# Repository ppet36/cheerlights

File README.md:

# Cheerlights coaster

Sources and models for Cheerlights coaster. Here is schematic + PCB layout files for my build of Cheerlights coaster as well as OpenSCAD model for enclosure and source code for ESP8266.

Build video https://www.youtube.com/watch?v=22OCCYykrT4

You need ESP8266-01 from eBay, WS2812B RGB digital LED, 3x10K resistor, 2x100n + 2x470u capacitor, 2x4 PINHD connector + standard 5.5/2.1 power conector (male and female) - beware that i made mistake in design schematic/PCB and power connector has -inside and +outside of the plug.

For build in Arduino you need FastLED library; https://github.com/FastLED/FastLED

### Some images

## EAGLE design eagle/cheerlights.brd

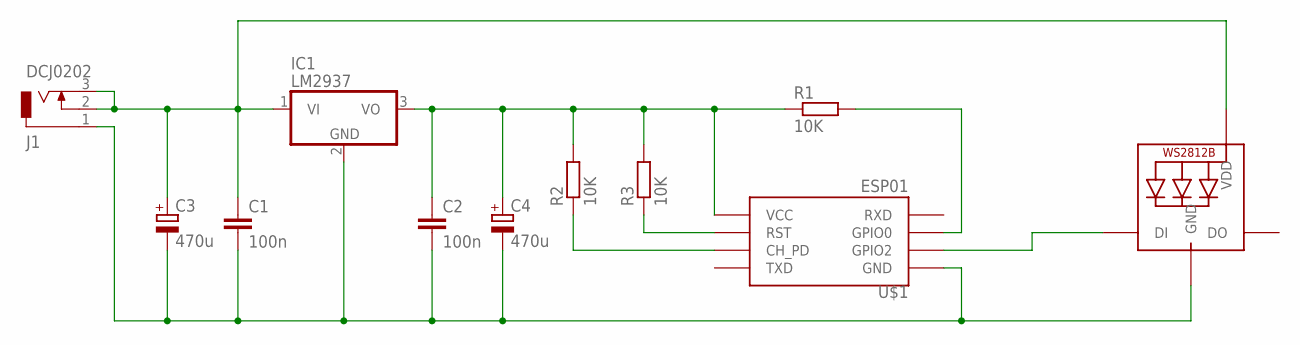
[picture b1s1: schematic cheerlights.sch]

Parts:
C1, C2: 100n; C050-025X075
C3, C4: 470u; E5-10,5
IC1: LM2937; TO220H
J1: DCJ0202
LED1: WS2812B_5050N; WS2812B-NARROW
R1: 10K; 0207/10
R2, R3: 10K; 0207/15
U$1: ESP01

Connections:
unnamed: C1.1, C3.+, IC1.1 (VI), J1.2, J1.3, LED1.1-VDD (VDD)
unnamed: C1.2, C2.2, C3.-, C4.-, IC1.2 (GND), J1.1, LED1.3-GND (GND), U$1.GND
unnamed: C2.1, C4.+, IC1.3 (VO), R1.1, R2.2, R3.2, U$1.VCC
unnamed: R1.2, U$1.GPIO0
unnamed: R3.1, U$1.RST
unnamed: R2.1, U$1.CH_PD
unnamed: LED1.4-DIN (DI), U$1.GPIO2

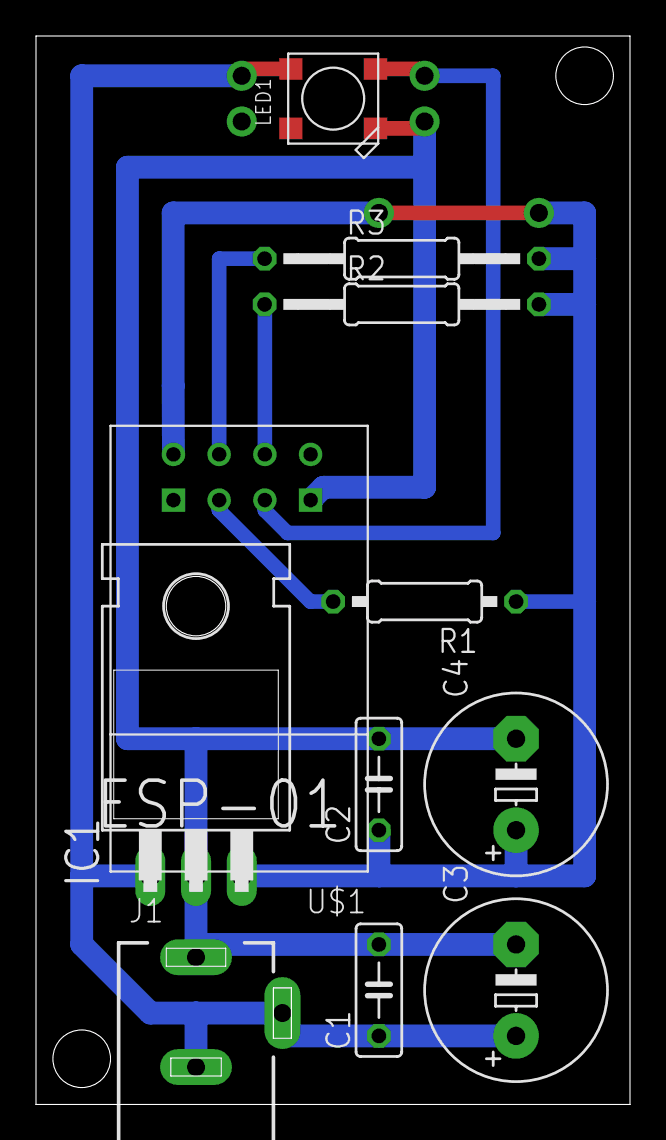
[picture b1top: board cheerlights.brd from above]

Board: 2 copper layers, 33.0 x 59.4 mm, 11 parts (0 on the bottom side), 7 nets.

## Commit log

2016-12-12 Update to use standard WiFi instead of WiFiMulti
    I made this change because i need to connect also hidden SSIDs
2016-12-12 Added some more configuration options
    I added configuration option for smoothing transition of colors and for brighten green and purple colors.
2019-07-18 Fix color parsing from response
